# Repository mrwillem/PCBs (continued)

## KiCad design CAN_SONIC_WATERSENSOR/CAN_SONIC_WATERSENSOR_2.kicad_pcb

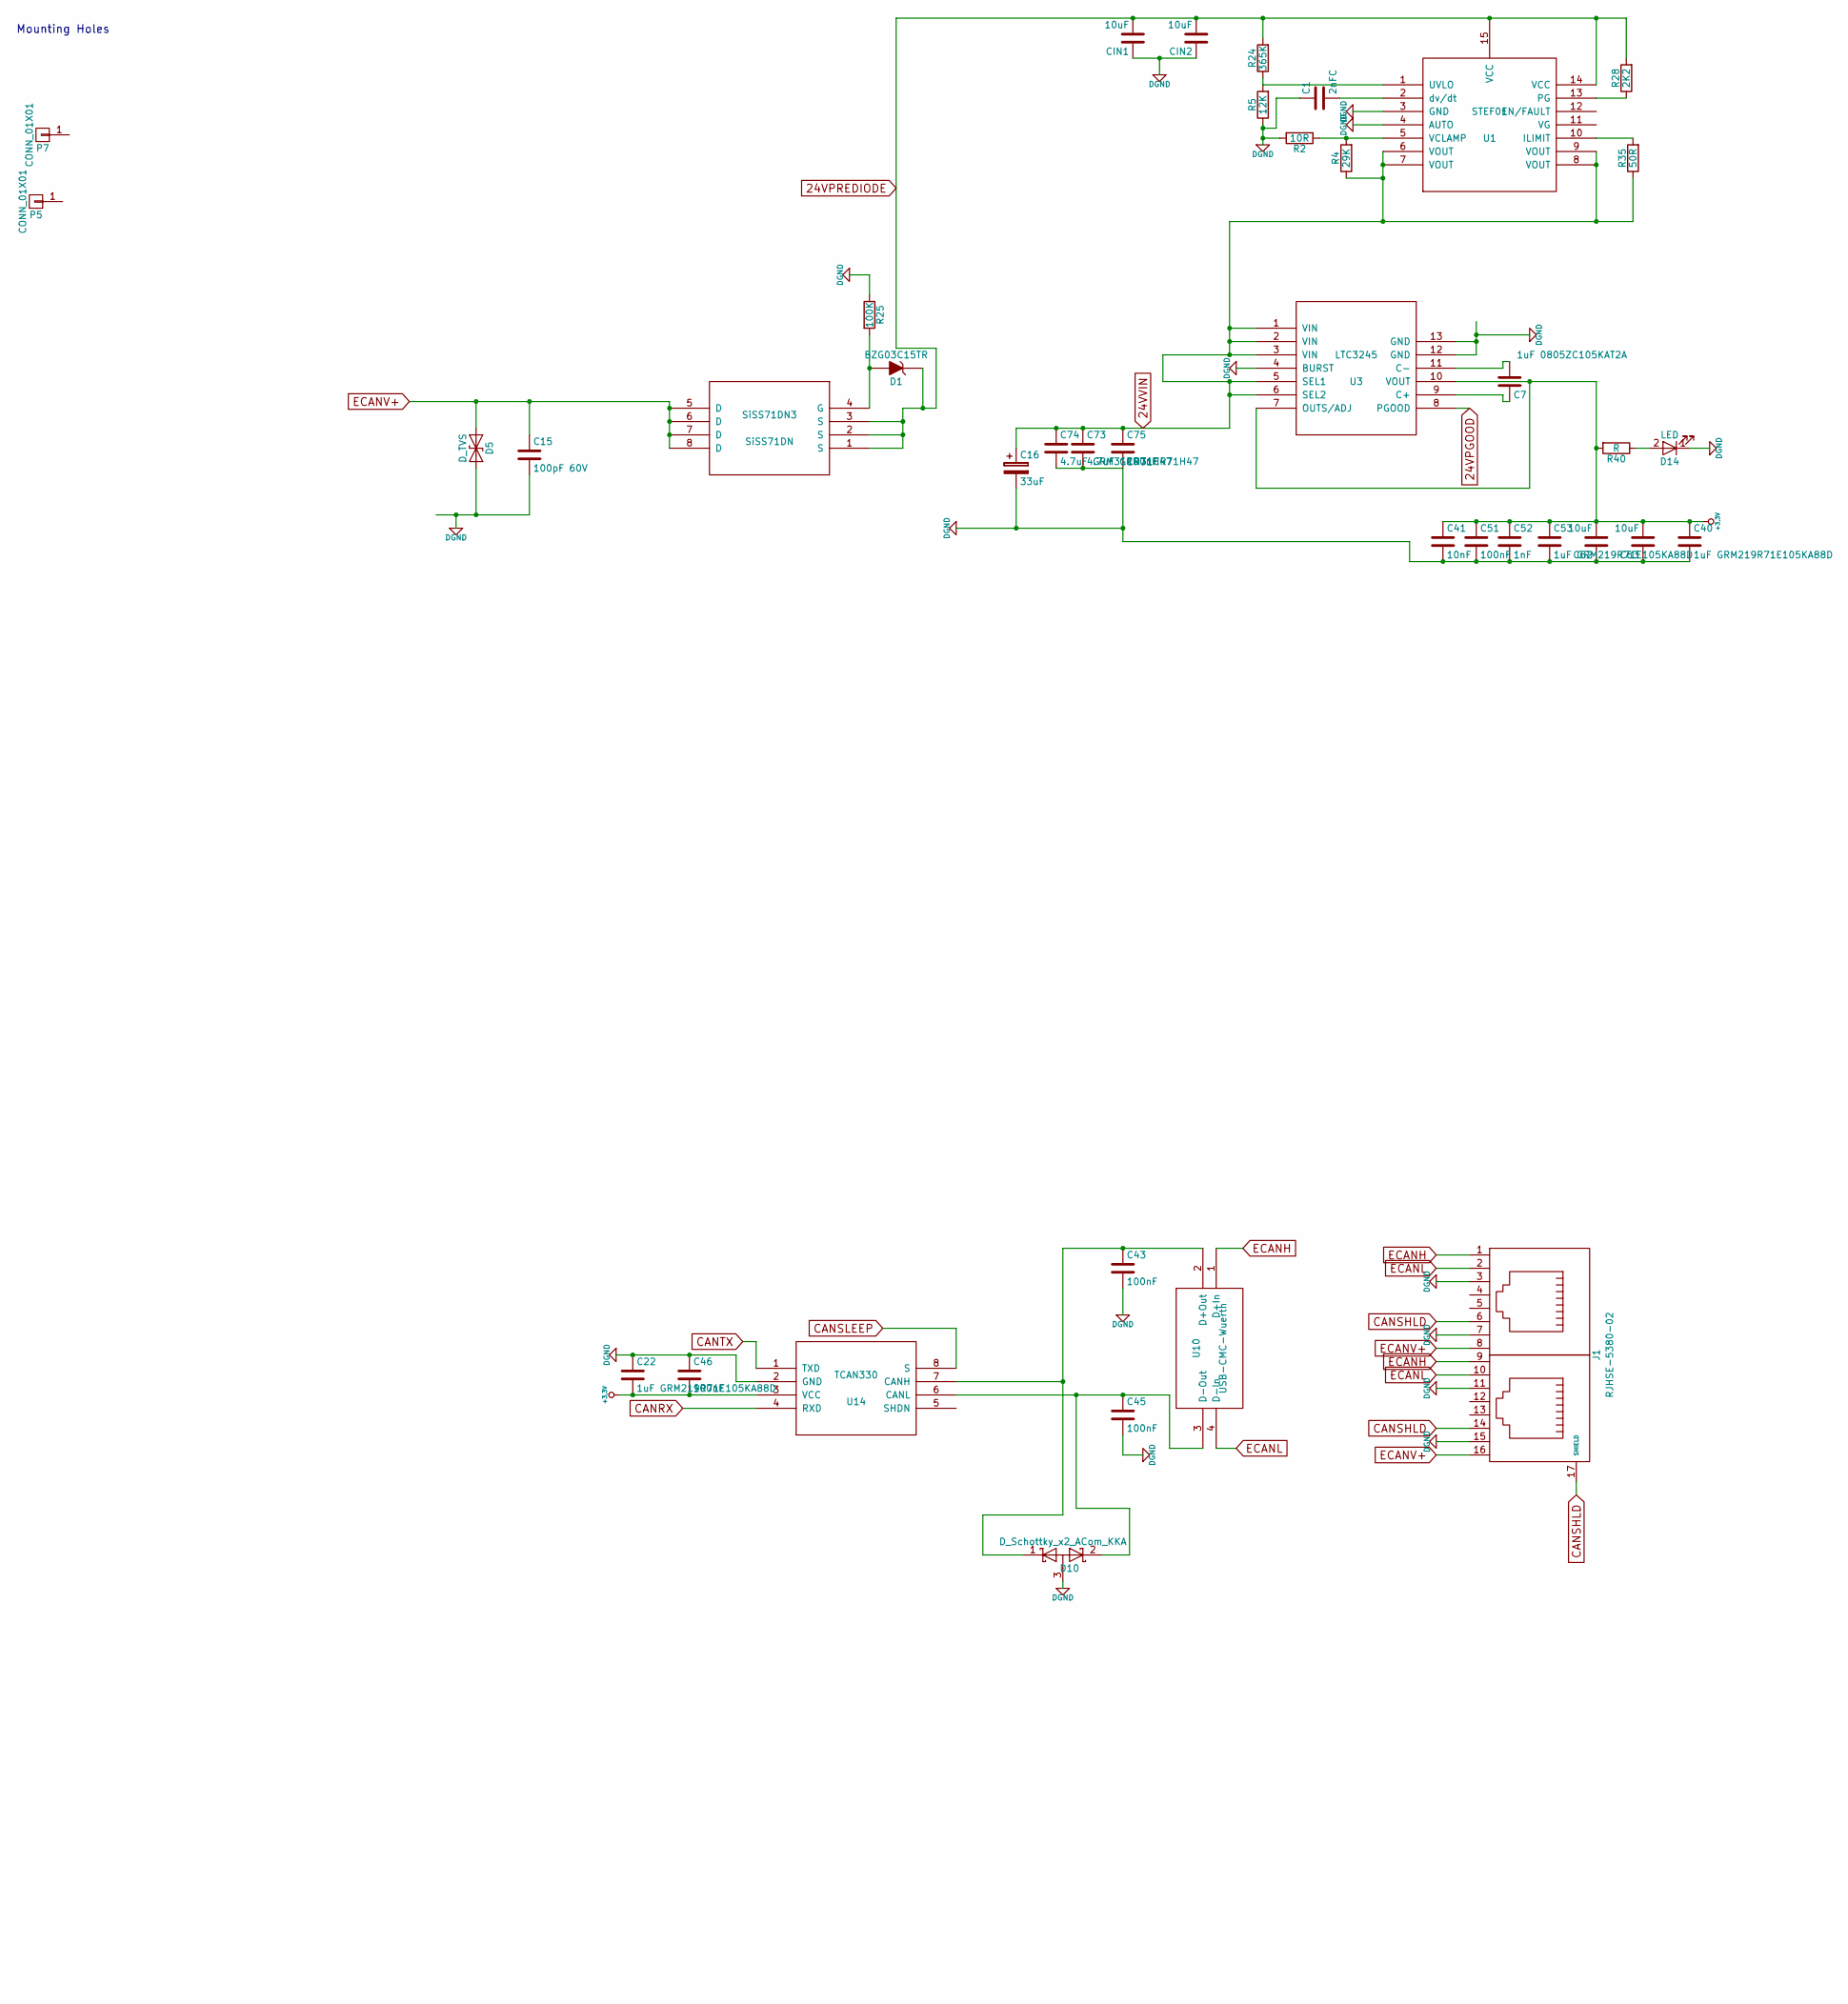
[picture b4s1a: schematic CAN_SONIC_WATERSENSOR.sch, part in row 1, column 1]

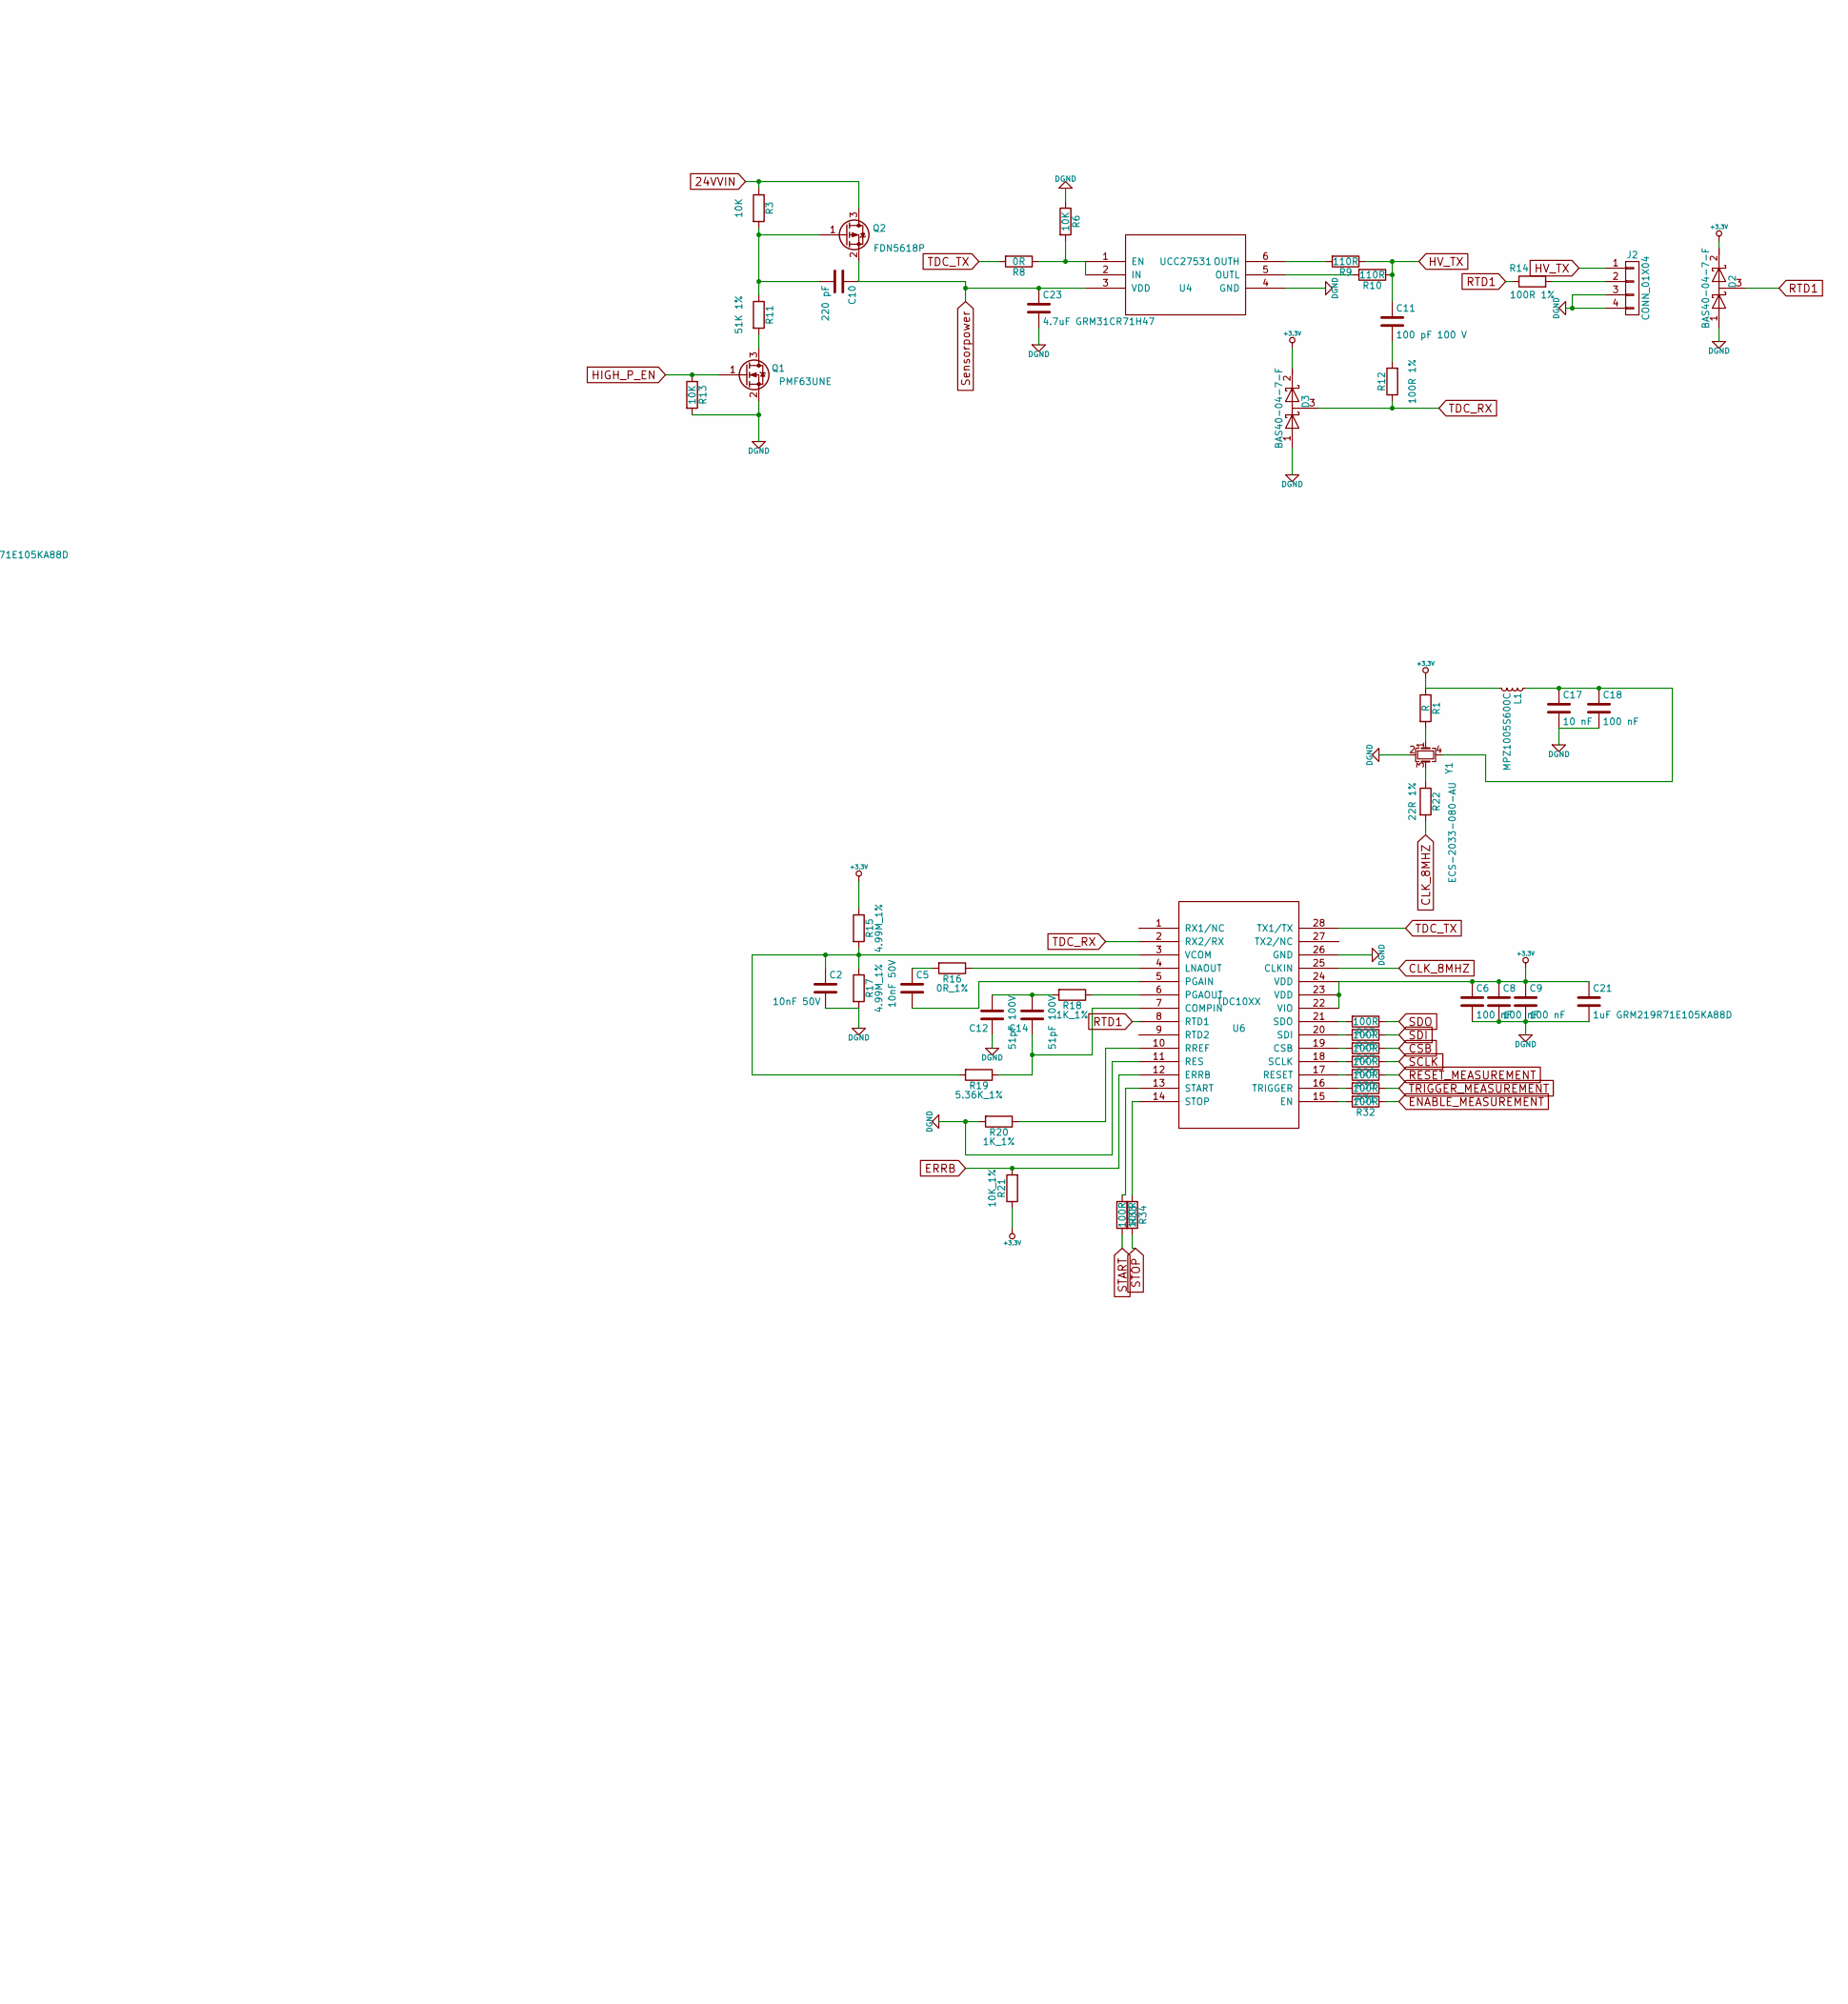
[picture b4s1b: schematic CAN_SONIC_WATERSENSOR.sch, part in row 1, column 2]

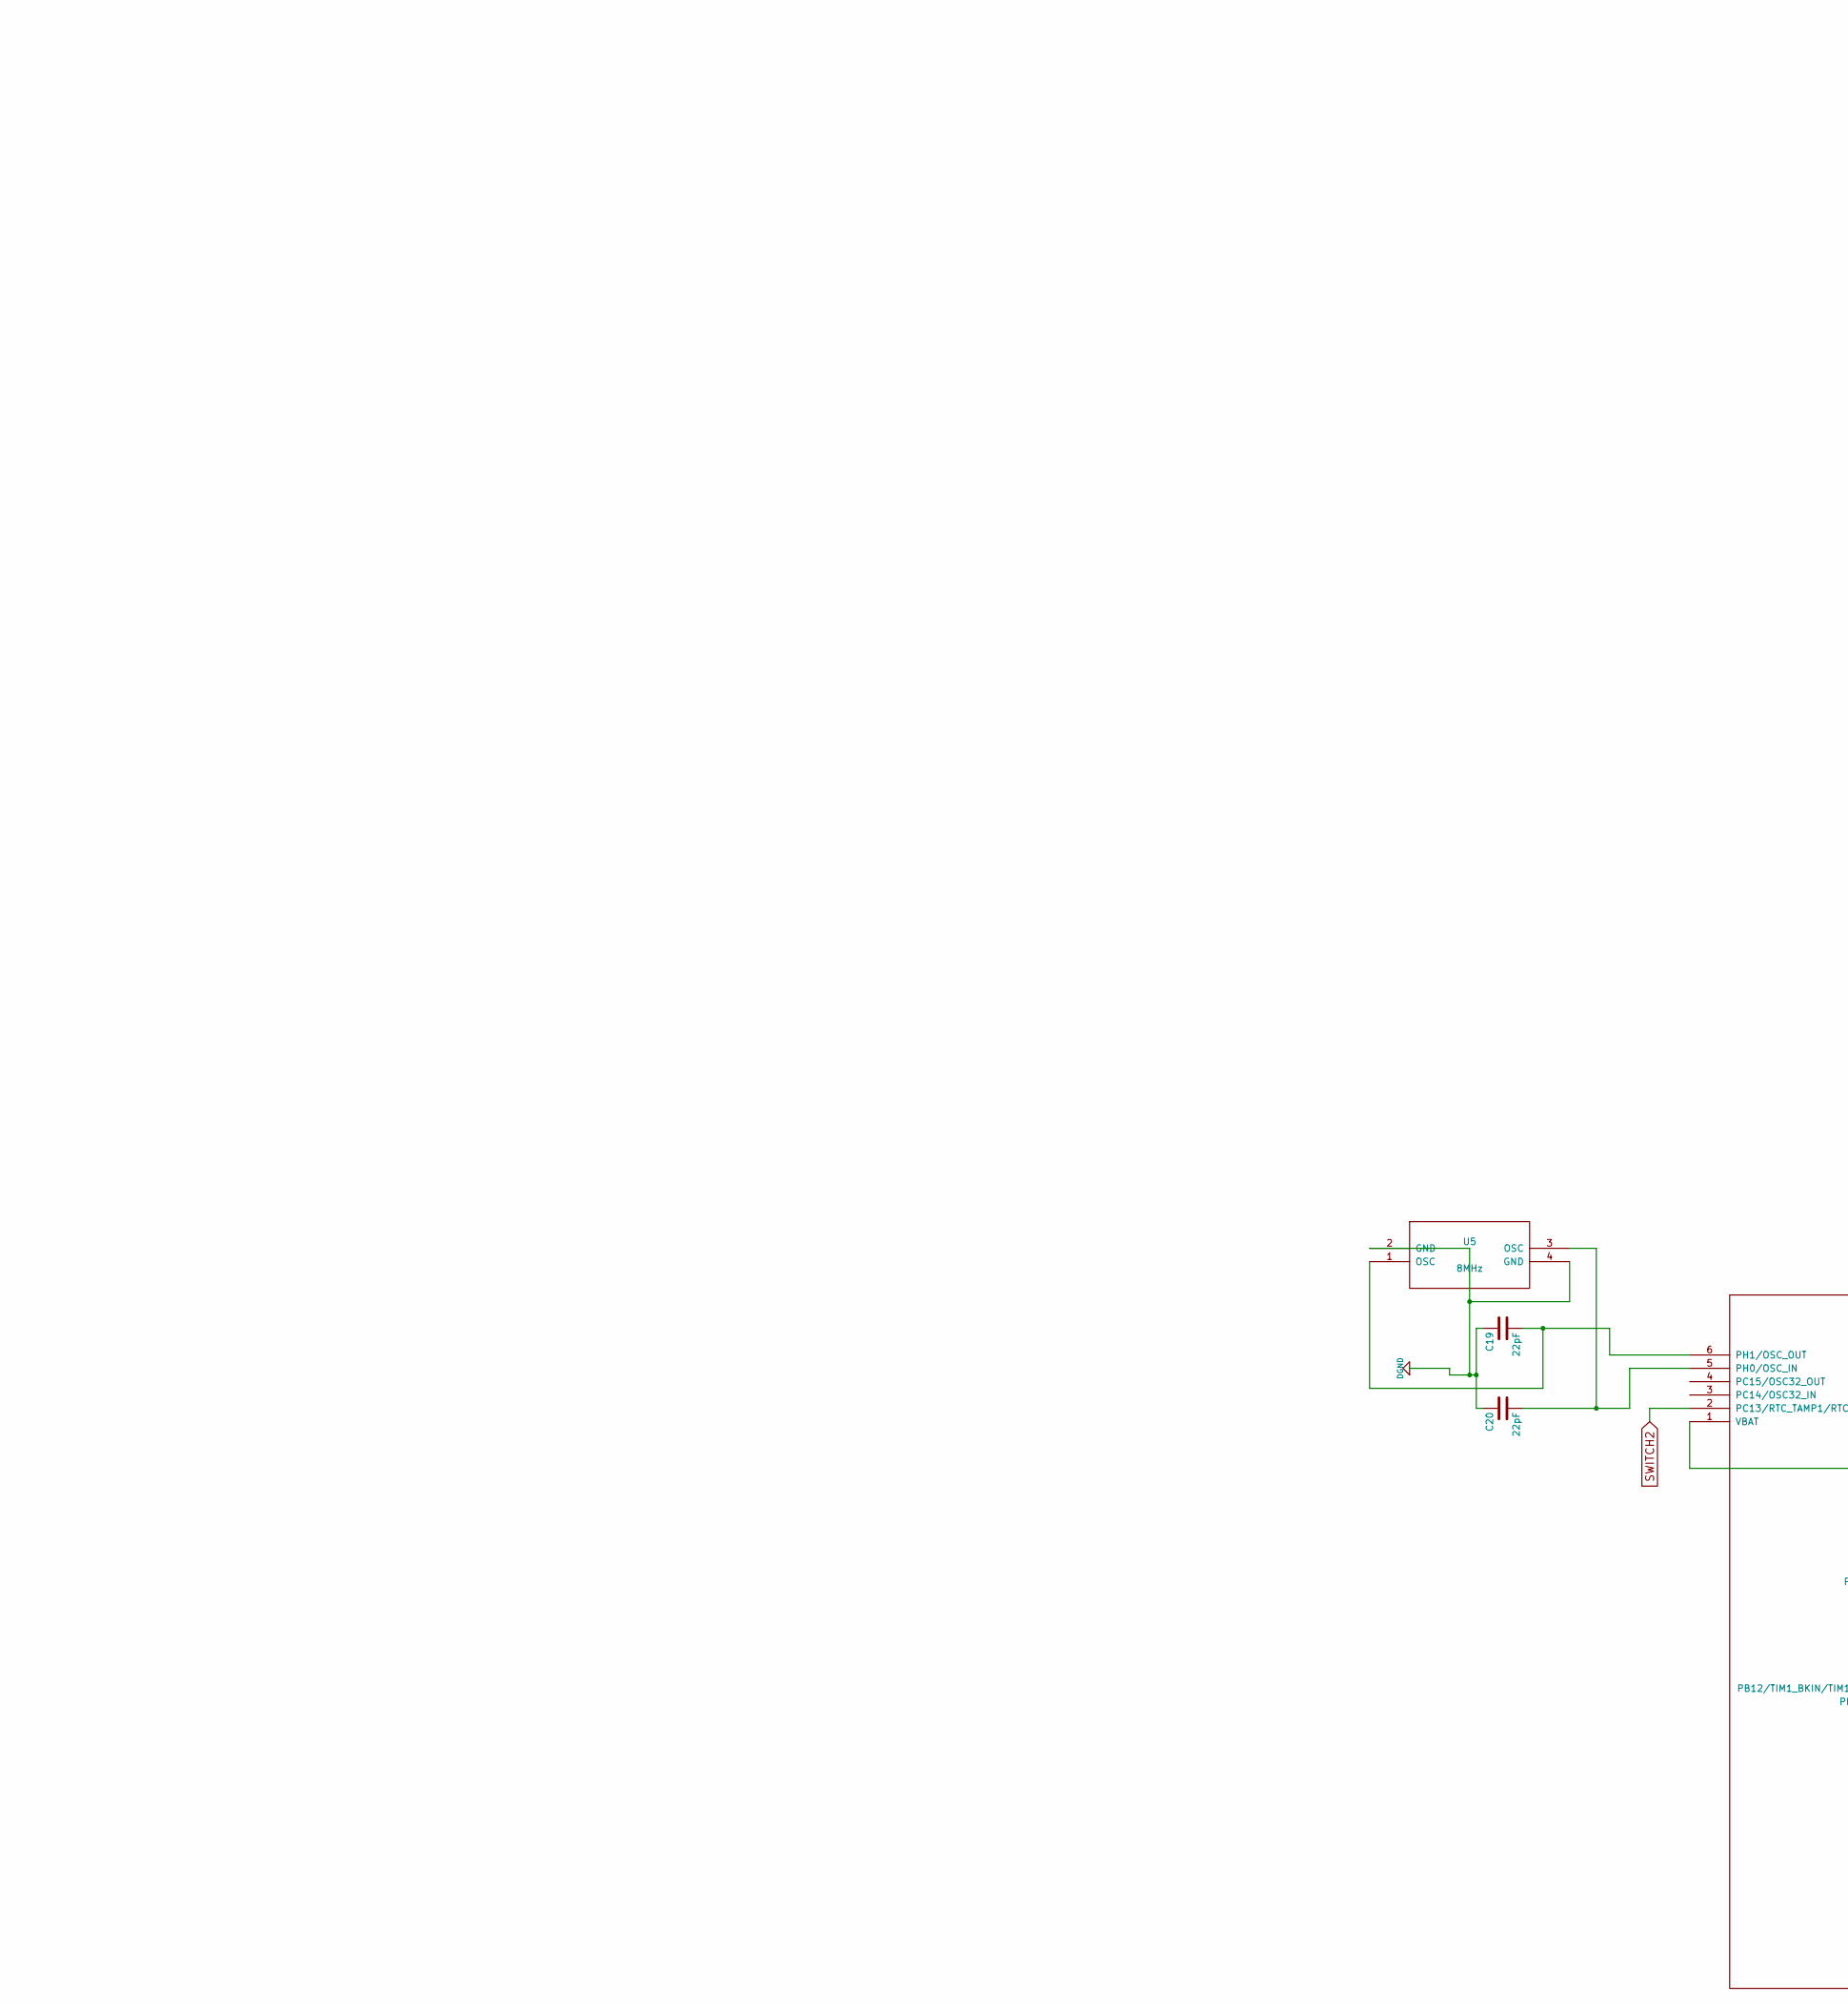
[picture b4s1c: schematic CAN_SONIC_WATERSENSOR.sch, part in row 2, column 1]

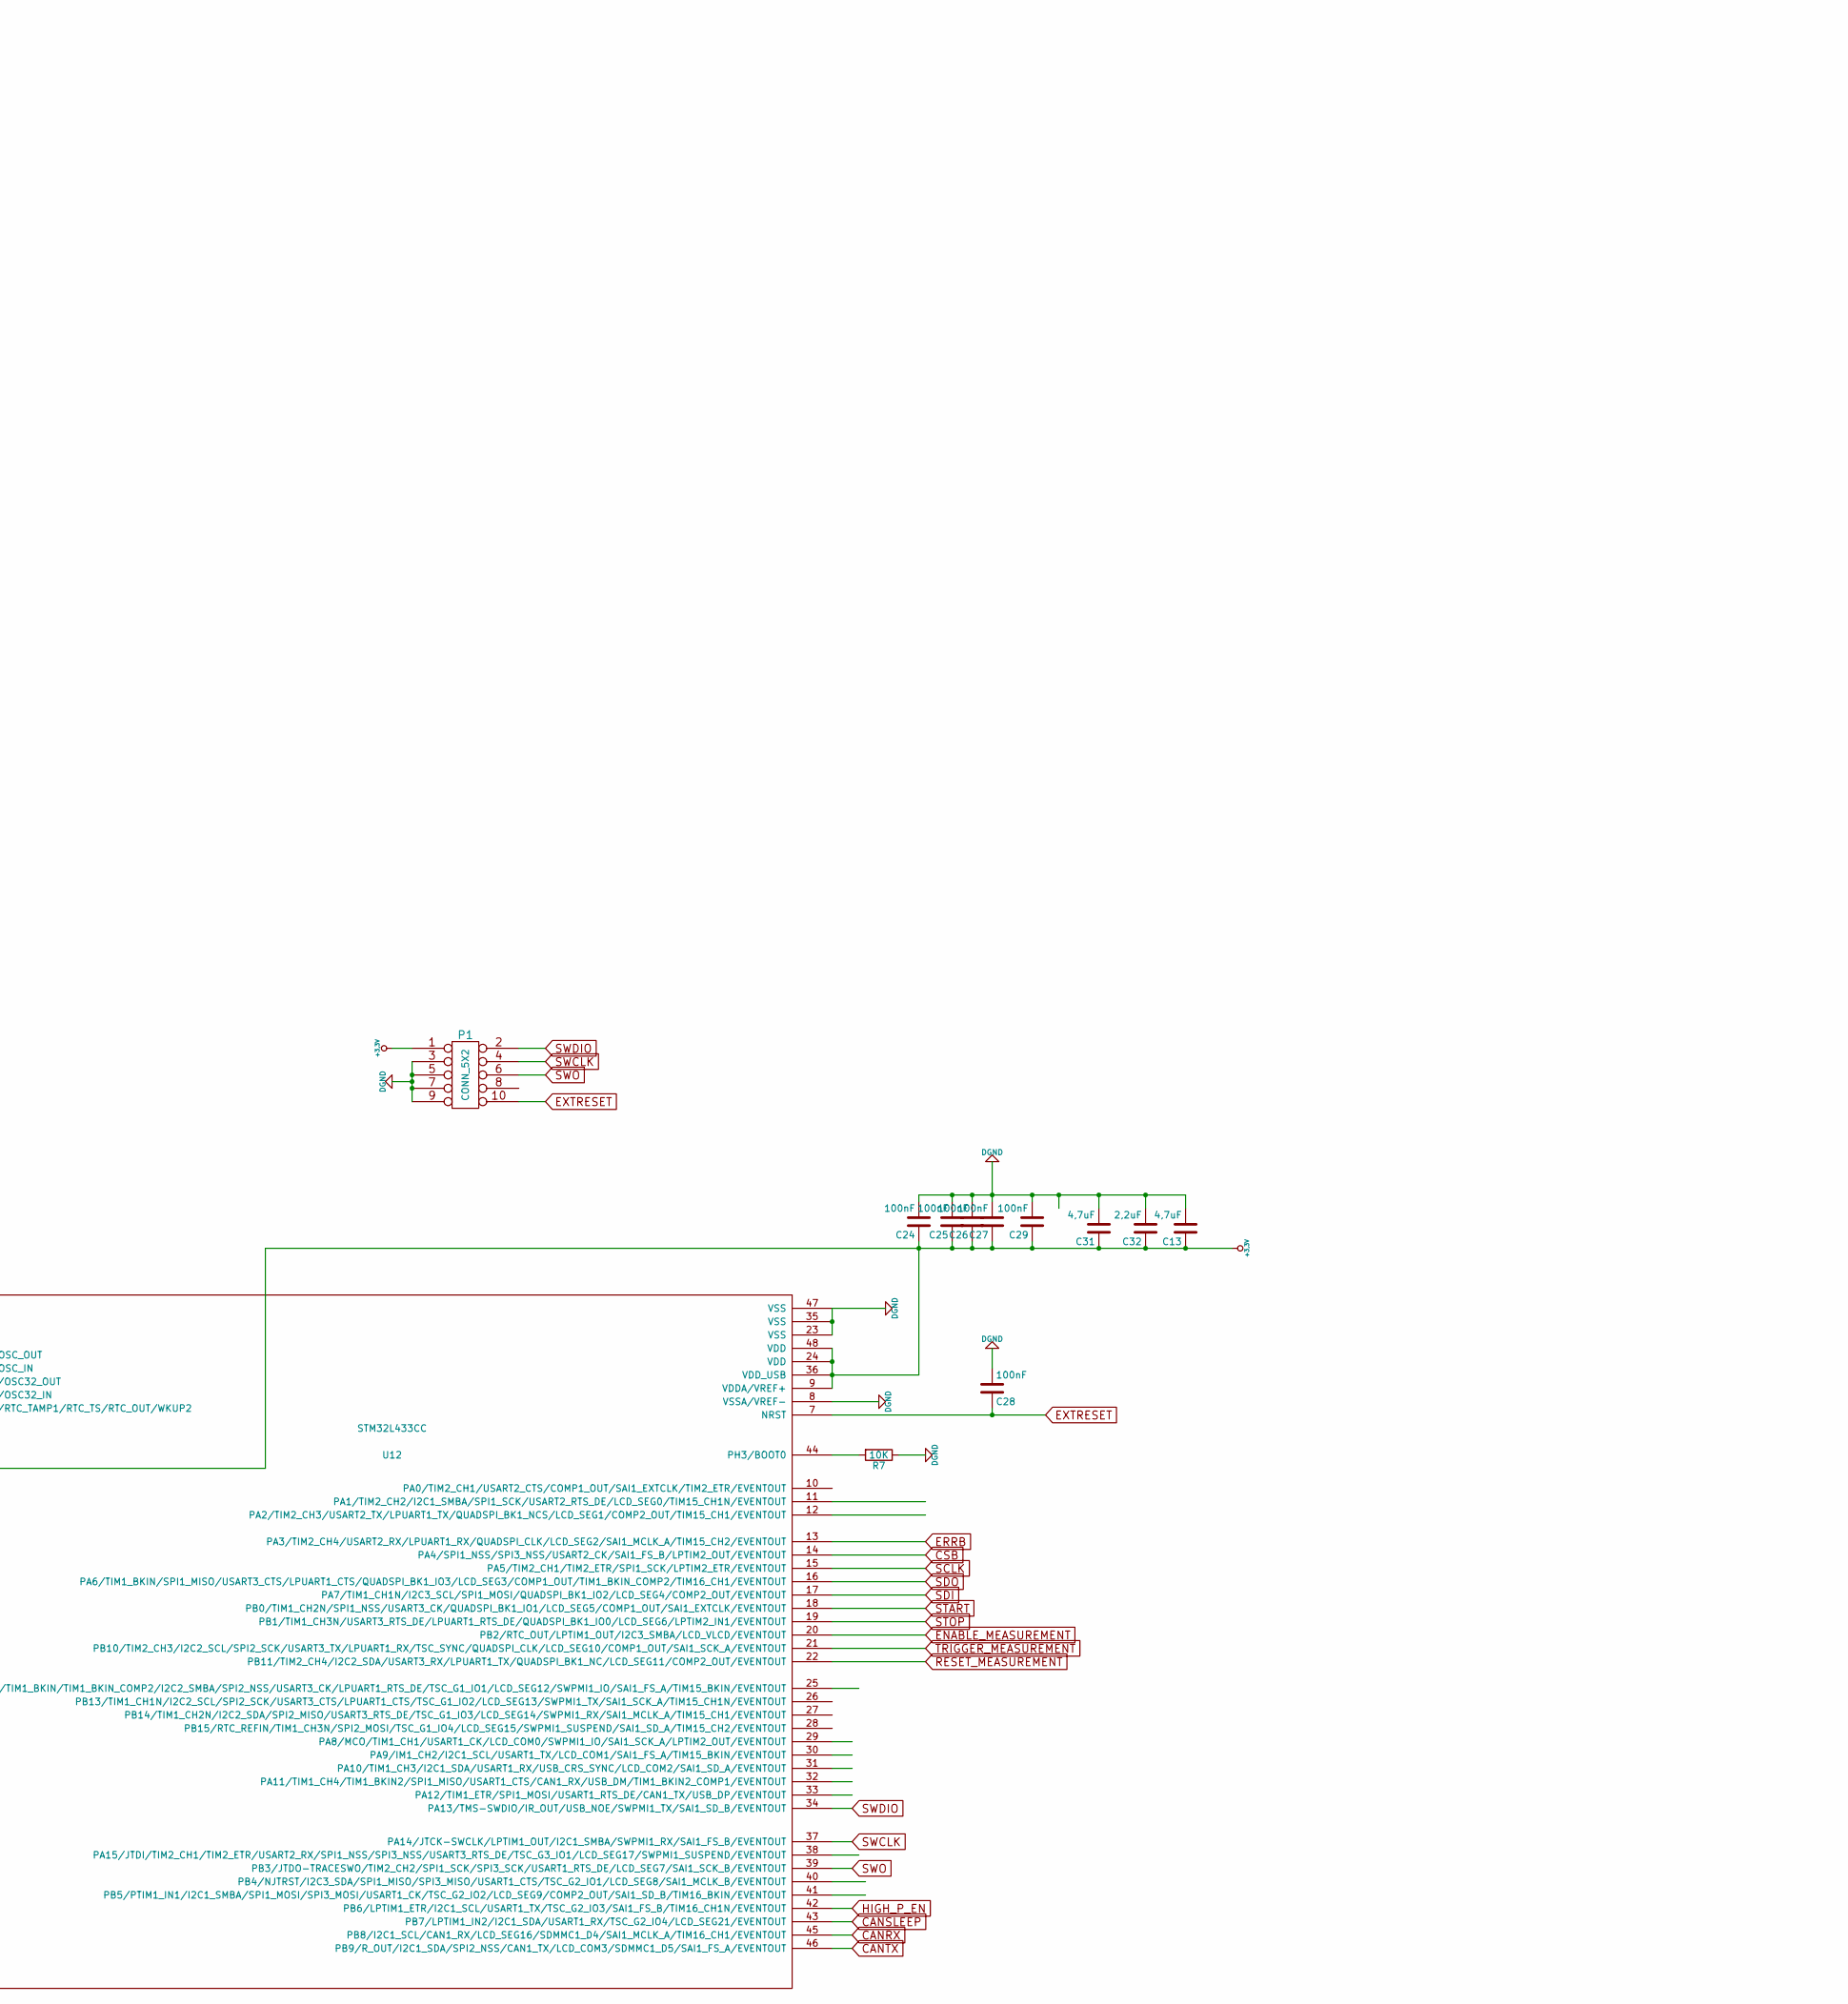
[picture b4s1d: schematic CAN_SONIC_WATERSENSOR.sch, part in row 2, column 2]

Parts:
C1: 2nFC; C_0805
C2, C5: 10nF 50V; R_0603_HandSolder
C6, C8, C9, C18: 100 nF; R_0603_HandSolder
C7: 1uF 0805ZC105KAT2A; C_0805
C10: 220 pF; R_0603_HandSolder
C11: 100 pF 100 V; R_0603_HandSolder
C12, C14: 51pF 100V; R_0603_HandSolder
C13, C31: 4,7uF; C_0805
C15: 100pF 60V; C_0805
C16: 33uF; CP_Elec_6.3x7.7
C17: 10 nF; R_0603_HandSolder
C19, C20: 22pF; R_0603_HandSolder
C21, C22, C40, C53: 1uF GRM219R71E105KA88D; C_0805
C23, C73, C74: 4.7uF GRM31CR71H47; C_1206
C24, C25, C26, C27, C28, C29, C43, C45, C46, C75: 100nF; R_0603_HandSolder
C32: 2,2uF; C_0805
C41: 10nF; C_0805
C51: 100nF; C_0805
C52: 1nF; C_0805
C62, C63: 10uF; C_0805
CIN1, CIN2: 10uF; C_2220_HandSoldering
D1: BZG03C15TR; D_SMA_Standard
D2, D3: BAS40-04-7-F; SOT-23
D5: D_TVS; D_SMB_Standard
D10: D_Schottky_x2_ACom_KKA; SOT-23
D14: LED; LED_0805
J1: RJHSE-5380-02; RJHSE538X-02-noled
J2: CONN_01X04; Molex_NanoFit_2x02x2.50mm_Angled
L1: MPZ1005S600C; R_0402_HandSoldering
P1: CONN_5X2; Pin_Header_Straight_2x05_Pitch1.27mm
P5, P7: CONN_01X01; MountingHole_2.5mm
Q1: PMF63UNE; SOT-323_SC-70_Handsoldering
Q2: FDN5618P; SuperSOT-3
R1: R; R_0603_HandSolder
R2: 10R; R_0805_HandSolder
R3, R6, R13: 10K; R_0603_HandSolder
R4: 29K; R_0805_HandSolder
R5: 12K; R_0805_HandSolder
R7: 10K; R_0805_HandSolder
R8: 0R; R_0603_HandSolder
R9, R10: 110R; R_0603_HandSolder
R11: 51K 1%; R_0603_HandSolder
R12, R14: 100R 1%; R_0603_HandSolder
R15, R17: 4.99M_1%; R_0603_HandSolder
R16: 0R_1%; R_0603_HandSolder
R18, R20: 1K_1%; R_0603_HandSolder
R19: 5.36K_1%; R_0603_HandSolder
R21: 10K_1%; R_0603_HandSolder
R22: 22R 1%; R_0603_HandSolder
R23, R26, R27, R29, R30, R31, R32, R33, R34: 100R; R_0603_HandSolder
R24: 365K; R_0805_HandSolder
R25: 100K; R_0603_HandSolder
R28: 2K2; R_0603_HandSolder
R35: 50R; R_0805_HandSolder
R40: R; R_0805_HandSolder
SiSS71DN3: SiSS71DN; PowerPack1212-8S_Pitch0.65mm
U1: STEF01; TSSOP-14-1EP_4.4x5mm_Pitch0.65mm
U3: LTC3245; MSOP-12-1EP_3x4mm_Pitch0.65mm
U4: UCC27531; SOT-23-6
U5: 8MHz; Crystal_SMD_EuroQuartz_MT-4pin_3.2x2.5mm_hand
U6: TDC10XX; TSSOP-28_4.4x9.7mm_Pitch0.65mm
U10: USB-CMC-Wuerth; CMC-SMD-Wuerth
U12: STM32L433CC; LQFP-48_7x7mm_Pitch0.5mm
U14: TCAN330; SOIC-8_3.9x4.9mm_Pitch1.27mm
Y1: ECS-2033-080-AU; Crystal_SMD_ECS2025_Hand_Soldering

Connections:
24VPREDIODE: CIN1.2, CIN2.2, D1.1 (K), R24.2, R28.2, SiSS71DN3.1 (S), SiSS71DN3.2 (S), SiSS71DN3.3 (S), U1.14 (VCC), U1.15 (VCC)
24VVIN: C16.1, C73.1, C74.1, C75.1, Q2.3 (D), R3.1, R4.1, R35.1, U1.6 (VOUT), U1.7 (VOUT), U1.8 (VOUT), U1.9 (VOUT), U3.1 (VIN), U3.2 (VIN), U3.3 (VIN), U3.5 (SEL1), U3.6 (SEL2)
+3.3V: C6.1, C8.1, C9.1, C13.1, C21.1, C22.2, C24.1, C25.1, C26.1, C27.1, C29.1, C31.1, C32.1, C40.1, C41.1, C46.2, C51.1, C52.1, C53.1, C62.2, C63.2, D2.2 (K), D3.2 (K), L1.2, P1.1, R1.1, R15.1, R21.1, R40.2, U3.7 (OUTS/ADJ), U3.10 (VOUT), U6.22 (VIO), U6.23 (VDD), U6.24 (VDD), U12.1 (VBAT), U12.9 (VDDA/VREF+), U12.24 (VDD), U12.36 (VDD_USB), U12.48 (VDD), U14.3 (VCC)
CANRX: U12.45 (PB8/I2C1_SCL/CAN1_RX/LCD_SEG16/SDMMC1_D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), U14.4 (RXD)
CANSHLD: J1.6, J1.14, J1.17 (SHIELD)
CANSLEEP: U12.43 (PB7/LPTIM1_IN2/I2C1_SDA/USART1_RX/TSC_G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), U14.8 (S)
CANTX: U12.46 (PB9/R_OUT/I2C1_SDA/SPI2_NSS/CAN1_TX/LCD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), U14.1 (TXD)
CLK_8MHZ: R22.2, U6.25 (CLKIN)
CSB: R27.1, U12.14 (PA4/SPI1_NSS/SPI3_NSS/USART2_CK/SAI1_FS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)
DGND: C1.1, C2.2, C6.2, C8.2, C9.2, C12.1, C13.2, C15.2, C16.2, C17.2, C18.2, C19.1, C20.1, C21.2, C22.1, C23.2, C24.2, C25.2, C26.2, C27.2, C28.2, C29.2, C31.2, C32.2, C40.2, C41.2, C43.2, C45.2, C46.1, C51.2, C52.2, C53.2, C62.1, C63.1, C73.2, C74.2, C75.2, CIN1.1, CIN2.1, D2.1 (A), D3.1 (A), D5.2 (A2), D10.3 (A), D14.1 (K), J1.3, J1.7, J1.11, J1.15, J2.3, J2.4, P1.3, P1.5, P1.7, P1.9, Q1.2 (S), R2.2, R5.1, R6.1, R7.1, R13.2, R17.2, R20.2, R25.1, U1.3 (GND), U1.4 (AUTO), U3.4 (BURST), U3.12 (GND), U3.13 (GND), U4.4 (GND), U5.2 (GND), U5.4 (GND), U6.11 (RES), U6.26 (GND), U12.8 (VSSA/VREF-), U12.23 (VSS), U12.35 (VSS), U12.47 (VSS), U14.2 (GND), Y1.2
ECANH: J1.1, J1.9, U10.1 (D+In)
ECANL: J1.2, J1.10, U10.4 (D-In)
ECANV+: C15.1, D5.1 (A1), J1.8, J1.16, SiSS71DN3.5 (D), SiSS71DN3.6 (D), SiSS71DN3.7 (D), SiSS71DN3.8 (D)
ENABLE_MEASUREMENT: R32.1, U12.20 (PB2/RTC_OUT/LPTIM1_OUT/I2C3_SMBA/LCD_VL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)
ERRB: R21.2, U6.12 (ERRB), U12.13 (PA3/TIM2_CH4/USART2_RX/LPUART1_RX/QUADS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)
EXTRESET: C28.1, P1.10, U12.7 (NRST)
HIGH_P_EN: Q1.1 (G), R13.1, U12.42 (PB6/LPTIM1_ETR/I2C1_SCL/USART1_TX/TSC_G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)
HV_TX: C11.1, J2.1, R9.1, R10.1
unnamed: C1.2, U1.2 (dv/dt)
unnamed: C2.1, R15.2, R17.1, R19.2, U6.3 (VCOM)
unnamed: C5.1, R16.2
unnamed: C5.2, U6.5 (PGAIN)
unnamed: C7.1, U3.9 (C+)
unnamed: C7.2, U3.11 (C-)
unnamed: C10.2, Q2.1 (G), R3.2, R11.1
unnamed: C11.2, R12.2
unnamed: C12.2, C14.2, R18.2
unnamed: C14.1, R19.1, U6.7 (COMPIN)
unnamed: C17.1, C18.1, L1.1, Y1.4
unnamed: C19.2, U5.1 (OSC), U12.6 (PH1/OSC_OUT)
unnamed: C20.2, U5.3 (OSC), U12.5 (PH0/OSC_IN)
unnamed: C43.1, D10.1 (K), U10.2 (D+Out), U14.7 (CANH)
unnamed: C45.1, D10.2 (K), U10.3 (D-Out), U14.6 (CANL)
unnamed: D1.2 (A), R25.2, SiSS71DN3.4 (G)
unnamed: D14.2 (A), R40.1
unnamed: J2.2, R14.2
unnamed: Q1.3 (D), R11.2
unnamed: R1.2, Y1.1
unnamed: R2.1, R4.2, U1.5 (VCLAMP)
unnamed: R6.2, R8.1, U4.1 (EN), U4.2 (IN)
unnamed: R7.2, U12.44 (PH3/BOOT0)
unnamed: R9.2, U4.6 (OUTH)
unnamed: R10.2, U4.5 (OUTL)
unnamed: R16.1, U6.4 (LNAOUT)
unnamed: R18.1, U6.6 (PGAOUT)
unnamed: R20.1, U6.10 (RREF)
unnamed: R22.1, Y1.3
unnamed: R23.2, U6.21 (SDO)
unnamed: R5.2, R24.1, U1.1 (UVLO)
unnamed: R26.2, U6.20 (SDI)
unnamed: R27.2, U6.19 (CSB)
unnamed: R28.1, U1.13 (PG)
unnamed: R29.2, U6.18 (SCLK)
unnamed: R30.2, U6.17 (RESET)
unnamed: R31.2, U6.16 (TRIGGER)
unnamed: R32.2, U6.15 (EN)
unnamed: R33.1, U6.13 (START)
unnamed: R34.1, U6.14 (STOP)
unnamed: R35.2, U1.10 (ILIMIT)
RESET_MEASUREMENT: R30.1, U12.22 (PB11/TIM2_CH4/I2C2_SDA/USART3_RX/LPUART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)
RTD1: D2.3 (common), R14.1, U6.8 (RTD1)
SCLK: R29.1, U12.15 (PA5/TIM2_CH1/TIM2_ETR/SPI1_SCK/LPTIM2_E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)
SDI: R26.1, U12.17 (PA7/TIM1_CH1N/I2C3_SCL/SPI1_MOSI/QUADSP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)
SDO: R23.1, U12.16 (PA6/TIM1_BKIN/SPI1_MISO/USART3_CTS/LPUA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)
START: R33.2, U12.18 (PB0/TIM1_CH2N/SPI1_NSS/USART3_CK/QUADSP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)
STOP: R34.2, U12.19 (PB1/TIM1_CH3N/USART3_RTS_DE/LPUART1_RTS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)
SWCLK: P1.4, U12.37 (PA14/JTCK-SWCLK/LPTIM1_OUT/I2C1_SMBA/SW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)
SWDIO: P1.2, U12.34 (PA13/TMS-SWDIO/IR_OUT/USB_NOE/SWPMI1_TX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)
SWO: P1.6, U12.39 (PB3/JTDO-TRACESWO/TIM2_CH2/SPI1_SCK/SPI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)
Sensorpower: C10.1, C23.1, Q2.2 (S), U4.3 (VDD)
TDC_RX: D3.3 (common), R12.1, U6.2 (RX2/RX)
TDC_TX: R8.2, U6.28 (TX1/TX)
TRIGGER_MEASUREMENT: R31.1, U12.21 (PB10/TIM2_CH3/I2C2_SCL/SPI2_SCK/USART3_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)

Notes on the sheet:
Mounting Holes

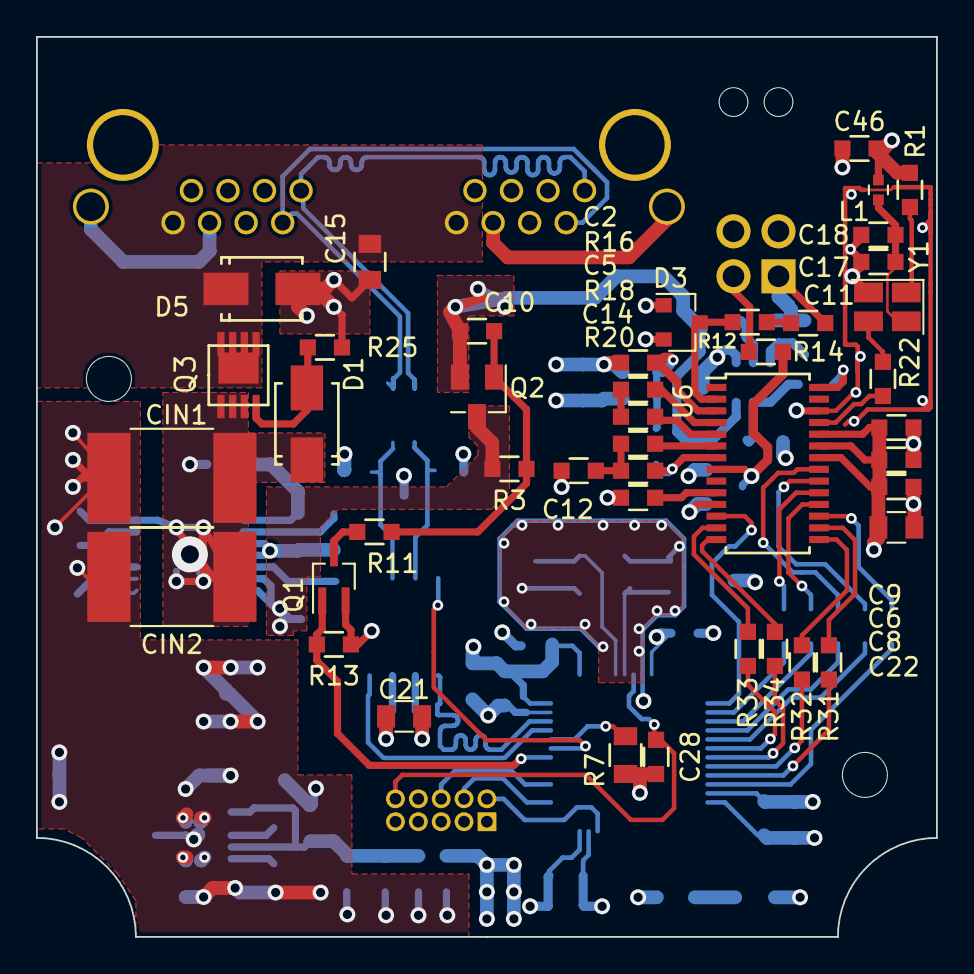
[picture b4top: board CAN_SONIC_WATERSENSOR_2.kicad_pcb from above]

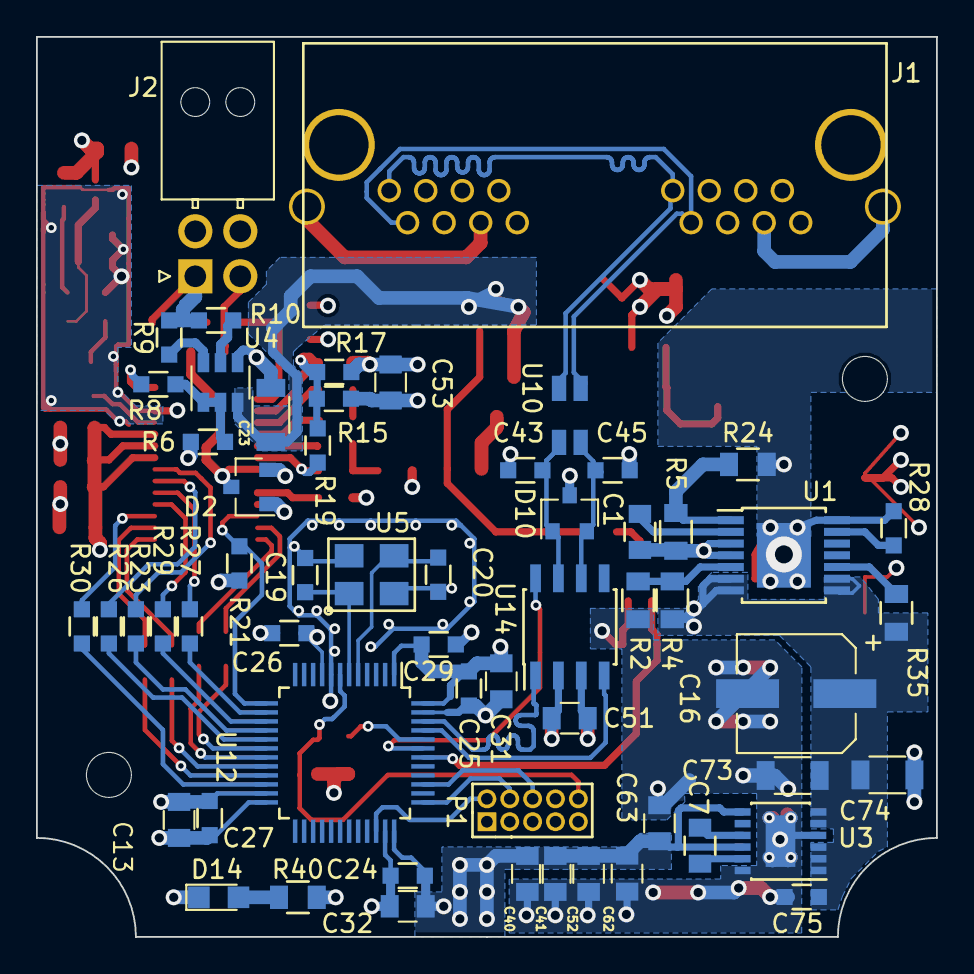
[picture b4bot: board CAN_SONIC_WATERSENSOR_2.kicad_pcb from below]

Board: 4 copper layers, 50.0 x 50.0 mm, 104 parts (59 on the bottom side), 73 nets.
